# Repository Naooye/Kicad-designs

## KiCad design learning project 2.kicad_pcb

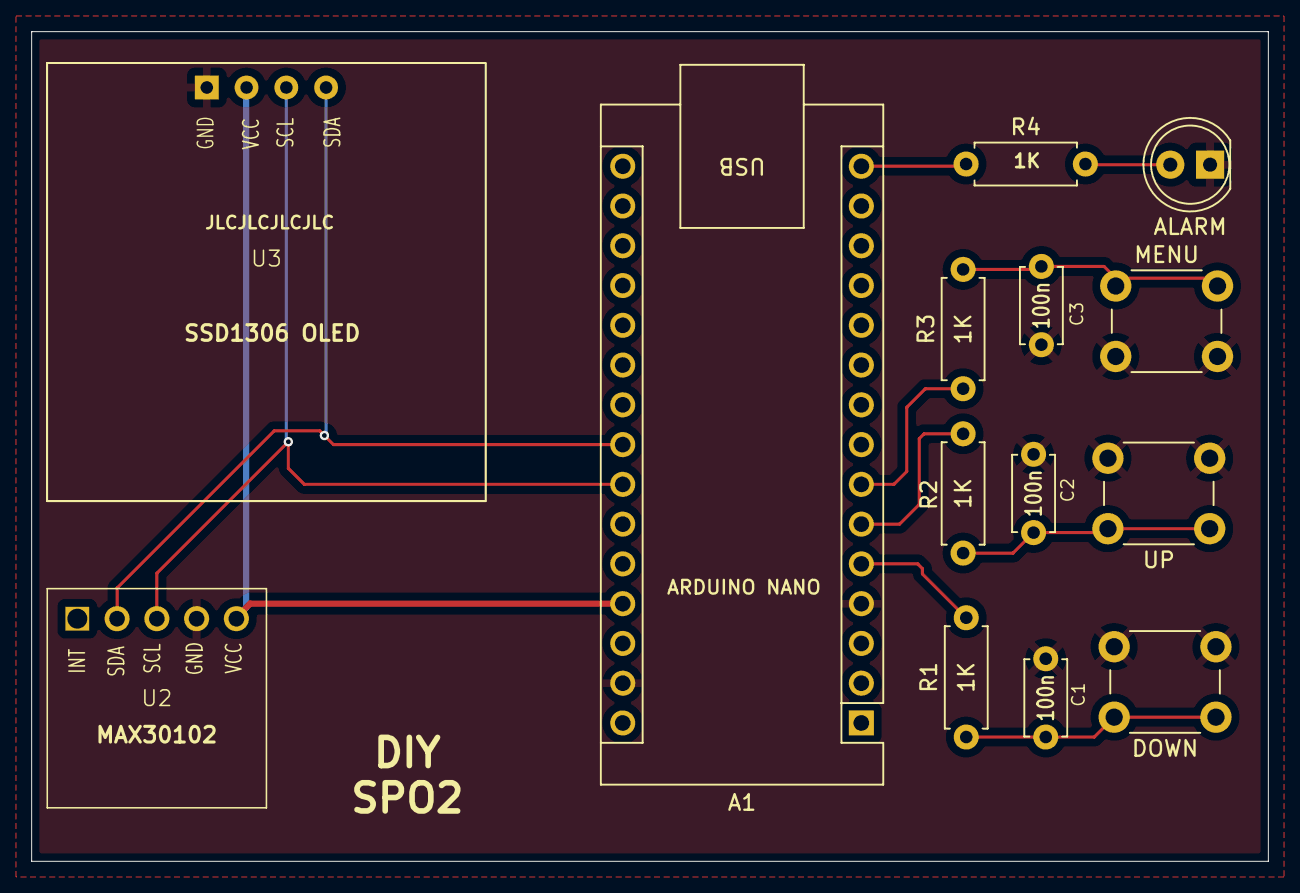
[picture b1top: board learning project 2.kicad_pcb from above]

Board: 2 copper layers, 79.0 x 53.0 mm, 14 parts (0 on the bottom side), 12 nets.

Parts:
A1: Arduino_Nano_v3.x; Arduino_Nano
ALARM: LED; LED_D5.0mm
C1, C2, C3: 100n; C_Disc_D4.7mm_W2.5mm_P5.00mm
DOWN: SW_Push; SW_PUSH_6mm
MENU: SW_Push; SW_PUSH_6mm
R1, R2, R3, R4: 1K; R_Axial_DIN0207_L6.3mm_D2.5mm_P7.62mm_Horizontal
U2: MAX30102X; MAX30102 MODULE
U3: SSD1306; SSD1306 LCD
UP: SW_Push; SW_PUSH_6mm

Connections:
+5V: A1.27 (+5V), U2.5 (VCC), U3.2 (VCC)
GND: A1.4 (GND), A1.29 (GND), ALARM.1 (K), C1.2, C2.2, C3.2, DOWN.2, MENU.2, U2.4 (GND), U3.1 (GND), UP.2
unnamed: A1.23 (A4), U2.2 (SDA), U3.4 (SDA)
unnamed: A1.24 (A5), U2.3 (SCL), U3.3 (SCL)
unnamed: A1.5 (D2), R1.1
unnamed: A1.6 (D3), R2.1
unnamed: A1.7 (D4), R3.1
unnamed: A1.15 (D12), R4.1
unnamed: C1.1, DOWN.1, R1.2
unnamed: C2.1, R2.2, UP.1
unnamed: C3.1, MENU.1, R3.2
unnamed: ALARM.2 (A), R4.2

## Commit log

2025-10-12 First version of my kicad tutorial design.
2025-10-15 Changed the number of pcb layers from 4 to 2.
